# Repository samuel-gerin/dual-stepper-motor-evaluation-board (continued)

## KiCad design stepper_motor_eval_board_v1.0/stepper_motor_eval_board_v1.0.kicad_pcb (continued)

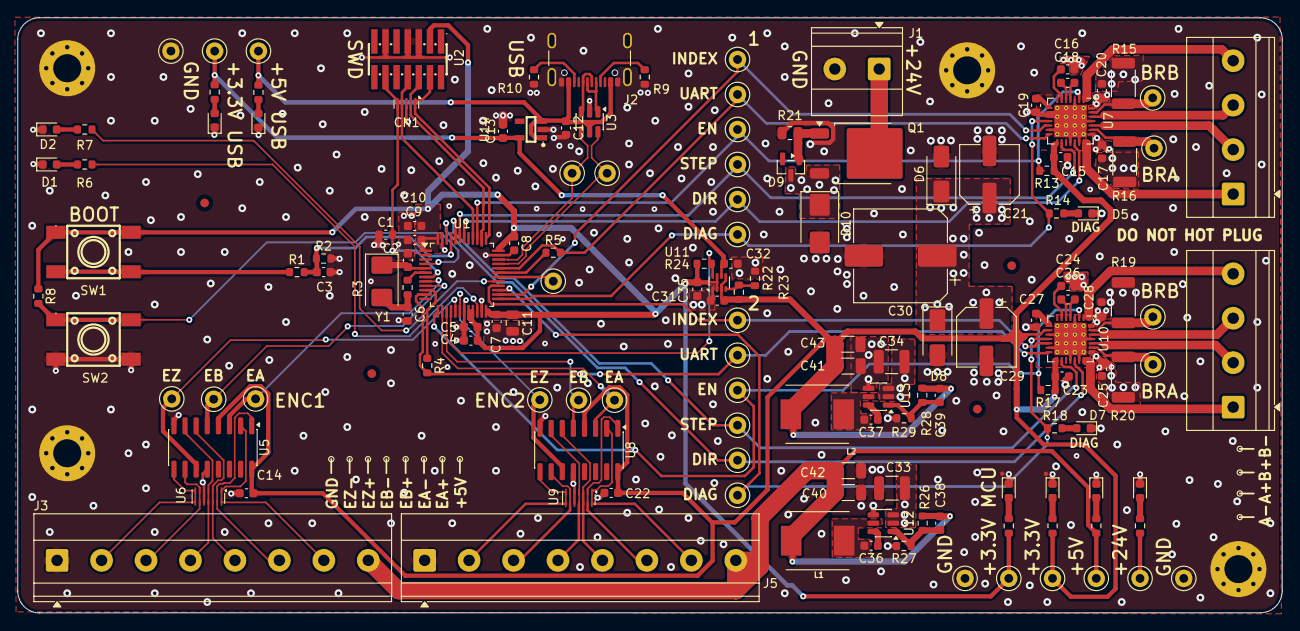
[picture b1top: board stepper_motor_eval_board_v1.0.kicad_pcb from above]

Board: 4 copper layers, 144.5 x 68.0 mm, 157 parts (0 on the bottom side), 98 nets.

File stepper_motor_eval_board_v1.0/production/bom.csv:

Designator,Footprint,Quantity,Value,LCSC Part #
"C1, C10, C14, C15, C16, C17, C20, C22, C23, C24, C25, C28, C3, C36, C37, C5, C7, C8, C9",0603,19,100n 50V,
"C11, C12, C13",0805,3,4u7 25V 0805,
"C18, C26",0603,2,22n 50V,
"C19, C27",0603,2,2.2µ 25V,
"C2, C6",0603,2,12p C0G 50V,
"C21, C29",CP_Elec_8x10,2,100µ 50V,
C30,CP_Elec_10x10.5,1,470µ 50V,
"C31, C32, C35, C4",0603,4,1µ 25V,
"C33, C34",1210,2,10µ 50V 1210,
"C38, C39",0603,2,100p C0G 50V,
"C40, C41, C42, C43",1206,4,22µ 25V 1206,
"D1, D11, D12, D13, D2, D3, D4, D5, D7",0603,9,R_LED,
D10,D_SMB,1,SMBJ24A,
"D6, D8",D_SMA,2,SMAJ24A,
D9,SOT-23,1,BZX84C15LT1G,
F1,Fuseholder_Cylinder-5x20mm_Schurter_0031_8201_Horizontal_Open,1,2A,
J2,USB_C_Receptacle_GCT_USB4105-xx-A_16P_TopMnt_Horizontal,1,USB_C_Receptacle_USB2.0_16P,
J3,"TerminalBlock_Phoenix_MKDS-1,5-8_1x08_P5.00mm_Horizontal",1,Encoder1_Conn,
J4,"TerminalBlock_Phoenix_MKDS-1,5-4_1x04_P5.00mm_Horizontal",1,Motor1_Conn,
J5,"TerminalBlock_Phoenix_MKDS-1,5-8_1x08_P5.00mm_Horizontal",1,Encoder2_Conn,
J6,"TerminalBlock_Phoenix_MKDS-1,5-4_1x04_P5.00mm_Horizontal",1,Motor2_Conn,
J7,DC-IN-TH_DC-012-5A-2.0,1,Barrel_Jack_Switch,C381117
J8,PinHeader_2x07_P1.27mm_Vertical_SMD,1,Conn_ST_STDC14,
L1,IND_ASPI-0630HI-3R3M-T15,1,10µ,
L2,IND_ASPI-0630HI-3R3M-T15,1,6µ8,
Q1,TO-252-2,1,SQD50P04-13L_T4GE3-HXY,
R1,0603,1,100,
"R10, R2, R9",0603,3,5k1,
"R11, R30",0603,2,1k5,
"R12, R14, R18, R31, R6, R7",0603,6,680,
"R13, R17, R24, R25",0603,4,10k,
"R15, R16, R19, R20",2010,4,220m 2010,
R21,0805,1,10 k,
R22,0603,1,180K,
R23,0603,1,100k,
R26,0603,1,157k,
R27,0603,1,30k,
R28,0603,1,196k,
R29,0603,1,62k,
R3,0603,1,0,
"R4, R5",0603,2,1k,
R8,0603,1,2k4,
"SW1, SW2",KEY-SMD_4P-L6.0-W6.0-P4.50-LS8.6,2,SW_Push,C381044
"TP1, TP10, TP11, TP12, TP13, TP14, TP15, TP16, TP17, TP18, TP19, TP2, TP20, TP21, TP22, TP23, TP24, TP25, TP26, TP27, TP28, TP29, TP3, TP30, TP31, TP32, TP33, TP34, TP35, TP36, TP37, TP38, TP39, TP4, TP40, TP41, TP42, TP43, TP44, TP45, TP46, TP47, TP48, TP49, TP5, TP50, TP51, TP52, TP53, TP54, TP55, TP6, TP7, TP8, TP9",TestPoint_Keystone_5000-5004_Miniature,55,TestPoint,
U1,LQFP-48_7x7mm_P0.5mm,1,STM32G431CBT6,
"U10, U7",VQFN-28-1EP_5x5mm_P0.5mm_EP3.7x3.7mm_ThermalVias,2,TMC2209-LA,
U11,SOT-583-8,1,TPS2116DRL,
"U12, U13",TSOT-23-6,2,AP63200WU-7,
U2,USON-10_2.5x1.0mm_P0.5mm,1,TPD4E05U06DQAR,
U3,SOT-23-6,1,USBLC6-2SC6,
U4,TSOT-23-5,1,MIC5365-3.3YD5,
"U5, U8",SOIC-16_3.9x9.9mm_P1.27mm,2,AM26LV32EIDRG4,
"U6, U9",Texas_R-PUSON-N14,2,TPD6E05U06RVZR,
Y1,Crystal_SMD_5032-2Pin_5.0x3.2mm,1,8MHz,
